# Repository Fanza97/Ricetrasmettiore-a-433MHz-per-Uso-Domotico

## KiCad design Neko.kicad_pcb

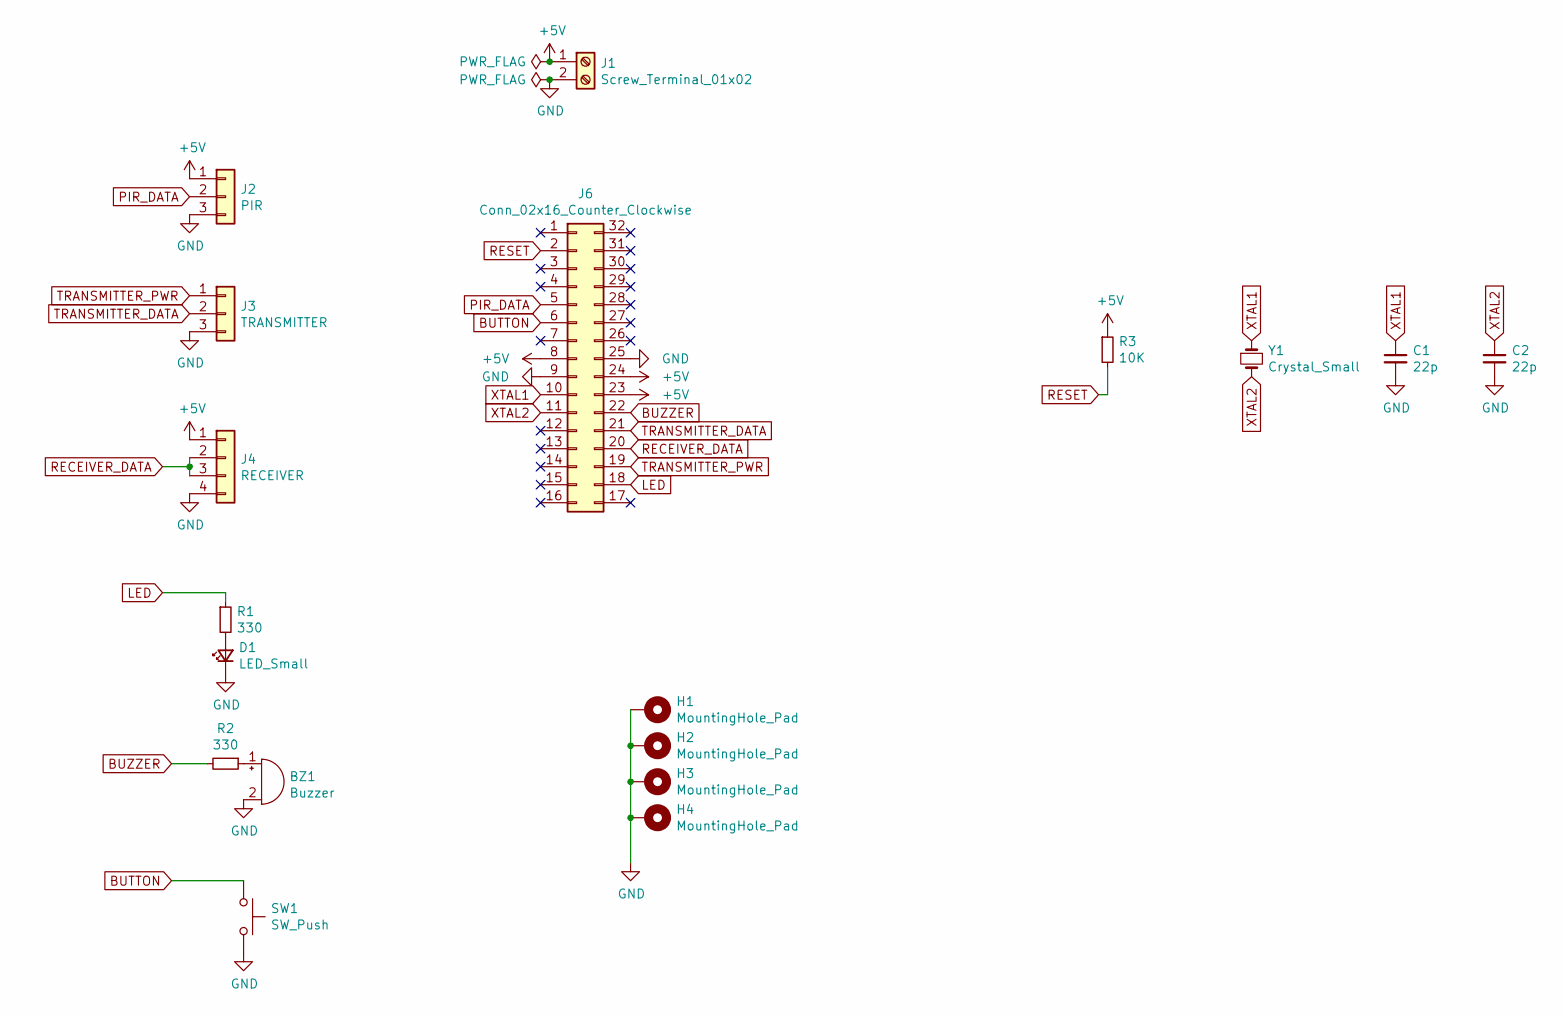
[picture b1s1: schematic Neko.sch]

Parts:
BZ1: Buzzer; Buzzer_15x7.5RM7.6
C1, C2: 22p; C_Disc_D3.0mm_W1.6mm_P2.50mm
D1: LED_Small; LED_D3.0mm
H1, H2, H3, H4: MountingHole_Pad; MountingHole_3.2mm_M3_Pad_Via
J1: Screw_Terminal_01x02; TerminalBlock_Phoenix_MPT-0,5-2-2.54_1x02_P2.54mm_Horizontal
J2: PIR; PinHeader_1x03_P2.54mm_Vertical
J3: TRANSMITTER; PinHeader_1x03_P2.54mm_Vertical
J4: RECEIVER; PinHeader_1x04_P2.54mm_Vertical
J6: Conn_02x16_Counter_Clockwise; DIP-32_W7.62mm
R1, R2: 330; R_Axial_DIN0207_L6.3mm_D2.5mm_P10.16mm_Horizontal
R3: 10K; R_Axial_DIN0207_L6.3mm_D2.5mm_P10.16mm_Horizontal
SW1: SW_Push; SW_PUSH_6mm
Y1: Crystal_Small; Crystal_HC18-U_Vertical

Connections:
+5V: J1.1, J2.1, J4.1, J6.8, J6.23, J6.24, R3.1
BUTTON: J6.6, SW1.1
BUZZER: J6.22, R2.2
GND: BZ1.2 (+), C1.2, C2.2, D1.1 (K), H1.1, H2.1, H3.1, H4.1, J1.2, J2.3, J3.3, J4.4, J6.9, J6.25, SW1.2
LED: J6.18, R1.1
unnamed: BZ1.1 (-), R2.1
unnamed: D1.2 (A), R1.2
PIR_DATA: J2.2, J6.5
RECEIVER_DATA: J4.2, J4.3, J6.20
RESET: J6.2, R3.2
TRANSMITTER_DATA: J3.2, J6.21
TRANSMITTER_PWR: J3.1, J6.19
XTAL1: C1.1, J6.10, Y1.1
XTAL2: C2.1, J6.11, Y1.2

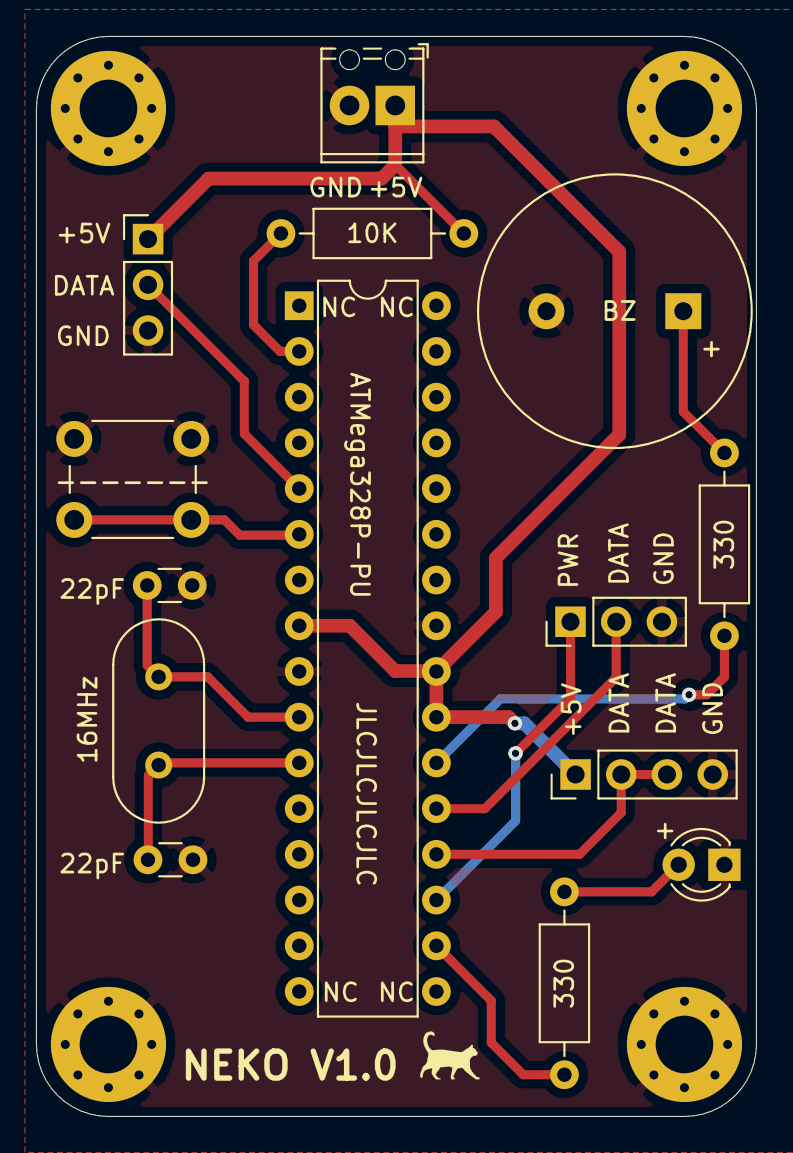
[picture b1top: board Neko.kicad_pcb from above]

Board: 2 copper layers, 40.0 x 60.0 mm, 18 parts (0 on the bottom side), 14 nets.
